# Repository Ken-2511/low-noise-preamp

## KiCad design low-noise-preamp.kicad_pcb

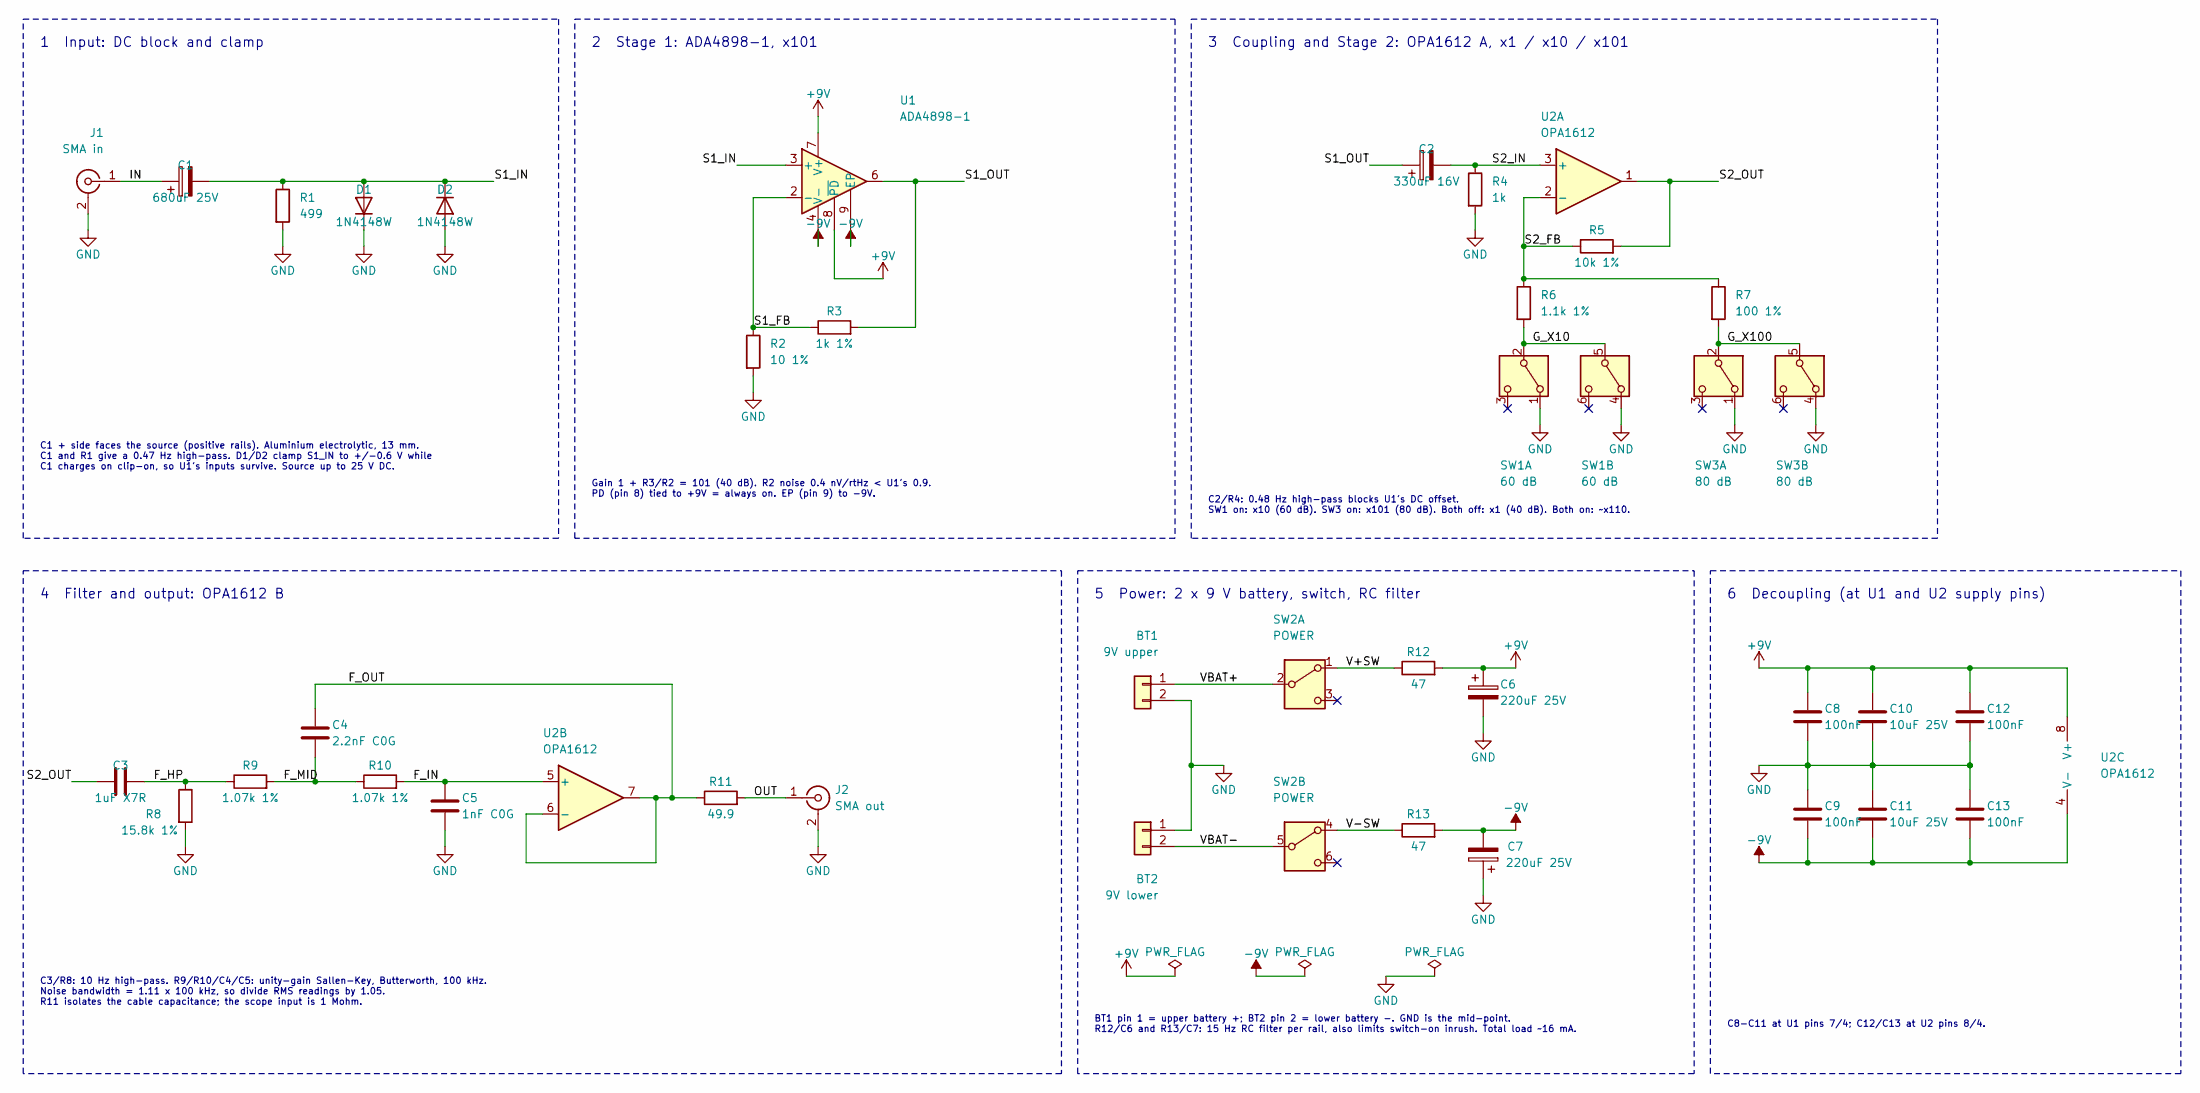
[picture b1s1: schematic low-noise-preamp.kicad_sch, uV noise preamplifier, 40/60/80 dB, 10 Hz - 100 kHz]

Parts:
BT1: 9V upper; JST_XH_B2B-XH-A_1x02_P2.50mm_Vertical
BT2: 9V lower; JST_XH_B2B-XH-A_1x02_P2.50mm_Vertical
C1: 680uF 25V; CP_Radial_D13.0mm_P5.00mm
C2: 330uF 16V; CP_Radial_D8.0mm_P3.50mm
C3: 1uF X7R; C_0805_2012Metric_Pad1.18x1.45mm_HandSolder
C4: 2.2nF C0G; C_0603_1608Metric_Pad1.08x0.95mm_HandSolder
C5: 1nF C0G; C_0603_1608Metric_Pad1.08x0.95mm_HandSolder
C6, C7: 220uF 25V; CP_Radial_D8.0mm_P3.50mm
C8, C9, C12, C13: 100nF; C_0603_1608Metric_Pad1.08x0.95mm_HandSolder
C10, C11: 10uF 25V; C_0805_2012Metric_Pad1.18x1.45mm_HandSolder
D1, D2: 1N4148W; D_SOD-123
J1: SMA in; SMA_Samtec_SMA-J-P-H-ST-EM1_EdgeMount
J2: SMA out; SMA_Samtec_SMA-J-P-H-ST-EM1_EdgeMount
R1: 499; R_0603_1608Metric_Pad0.98x0.95mm_HandSolder
R2: 10 1%; R_0603_1608Metric_Pad0.98x0.95mm_HandSolder
R3: 1k 1%; R_0603_1608Metric_Pad0.98x0.95mm_HandSolder
R4: 1k; R_0603_1608Metric_Pad0.98x0.95mm_HandSolder
R5: 10k 1%; R_0603_1608Metric_Pad0.98x0.95mm_HandSolder
R6: 1.1k 1%; R_0603_1608Metric_Pad0.98x0.95mm_HandSolder
R7: 100 1%; R_0603_1608Metric_Pad0.98x0.95mm_HandSolder
R8: 15.8k 1%; R_0603_1608Metric_Pad0.98x0.95mm_HandSolder
R9, R10: 1.07k 1%; R_0603_1608Metric_Pad0.98x0.95mm_HandSolder
R11: 49.9; R_0603_1608Metric_Pad0.98x0.95mm_HandSolder
R12, R13: 47; R_0805_2012Metric_Pad1.20x1.40mm_HandSolder
SW1: 60 dB; SW_Slide_DPDT_MSS-22D18
SW2: POWER; SW_Slide_DPDT_MSS-22D18
SW3: 80 dB; SW_Slide_DPDT_MSS-22D18
U1: ADA4898-1; SOIC-8-1EP_3.9x4.9mm_P1.27mm_EP2.29x3mm
U2: OPA1612; SOIC-8_3.9x4.9mm_P1.27mm

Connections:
+9V: C6.1, C8.1, C10.1, C12.1, R12.2, U1.7 (V+), U1.8 (~PD), U2.8 (V+)
-9V: C7.2, C9.2, C11.2, C13.2, R13.2, U1.4 (V-), U1.9 (EP), U2.4 (V-)
/F_HP: C3.2, R8.1, R9.1
/F_IN: C5.1, R10.2, U2.5 (+)
/F_MID: C4.2, R9.2, R10.1
/F_OUT: C4.1, R11.1, U2.6 (-), U2.7
/G_X10: R6.2, SW1.2 (B), SW1.5 (B)
/G_X100: R7.2, SW3.2 (B), SW3.5 (B)
/IN: C1.1, J1.1 (In)
/OUT: J2.1 (In), R11.2
/S1_FB: R2.1, R3.1, U1.2 (-)
/S1_IN: C1.2, D1.2 (A), D2.1 (K), R1.1, U1.3 (+)
/S1_OUT: C2.1, R3.2, U1.6
/S2_FB: R5.1, R6.1, R7.1, U2.2 (-)
/S2_IN: C2.2, R4.1, U2.3 (+)
/S2_OUT: C3.1, R5.2, U2.1
/V+SW: R12.1, SW2.1 (A)
/V-SW: R13.1, SW2.4 (A)
/VBAT+: BT1.1, SW2.2 (B)
/VBAT-: BT2.2, SW2.5 (B)
GND: BT1.2, BT2.1, C5.2, C6.2, C7.1, C8.2, C9.1, C10.2, C11.1, C12.2, C13.1, D1.1 (K), D2.2 (A), J1.2 (Ext), J2.2 (Ext), R1.2, R2.2, R4.2, R8.2, SW1.1 (A), SW1.4 (A), SW3.1 (A), SW3.4 (A); also elsewhere on the board

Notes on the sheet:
1 Input: DC block and clamp
C1 + side faces the source (positive rails). Aluminium electrolytic, 13 mm. C1 and R1 give a 0.47 Hz high-pass. D1/D2 clamp S1_IN to +/-0.6 V while C1 charges on clip-on, so U1's inputs survive. Source up to 25 V DC.
2 Stage 1: ADA4898-1, x101
Gain 1 + R3/R2 = 101 (40 dB). R2 noise 0.4 nV/rtHz < U1's 0.9. PD (pin 8) tied to +9V = always on. EP (pin 9) to -9V.
3 Coupling and Stage 2: OPA1612 A, x1 / x10 / x101
C2/R4: 0.48 Hz high-pass blocks U1's DC offset. SW1 on: x10 (60 dB). SW3 on: x101 (80 dB). Both off: x1 (40 dB). Both on: ~x110.
4 Filter and output: OPA1612 B
C3/R8: 10 Hz high-pass. R9/R10/C4/C5: unity-gain Sallen-Key, Butterworth, 100 kHz. Noise bandwidth = 1.11 x 100 kHz, so divide RMS readings by 1.05. R11 isolates the cable capacitance; the scope input is 1 Mohm.
5 Power: 2 x 9 V battery, switch, RC filter
BT1 pin 1 = upper battery +; BT2 pin 2 = lower battery -. GND is the mid-point. R12/C6 and R13/C7: 15 Hz RC filter per rail, also limits switch-on inrush. Total load ~16 mA.
6 Decoupling (at U1 and U2 supply pins)
C8-C11 at U1 pins 7/4; C12/C13 at U2 pins 8/4.

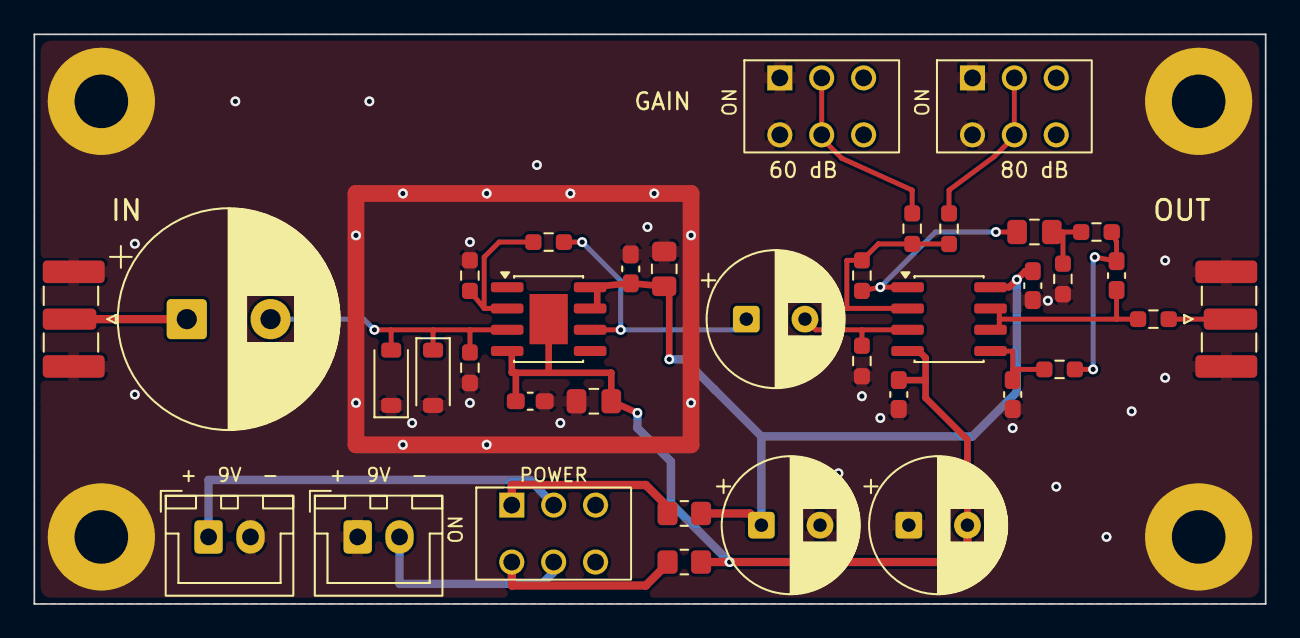
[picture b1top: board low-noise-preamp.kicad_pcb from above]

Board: 2 copper layers, 73.5 x 34.0 mm, 41 parts (0 on the bottom side), 21 nets.

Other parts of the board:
H1, H2, H3, H4: M3; MountingHole_3.2mm_M3_Pad

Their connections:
GND: H1.1, H2.1, H3.1, H4.1; also elsewhere on the board

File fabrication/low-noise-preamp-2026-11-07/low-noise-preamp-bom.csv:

"Refs","Value","Footprint","Qty"
"BT1","9V upper","Connector_JST:JST_XH_B2B-XH-A_1x02_P2.50mm_Vertical","1"
"BT2","9V lower","Connector_JST:JST_XH_B2B-XH-A_1x02_P2.50mm_Vertical","1"
"C1","680uF 25V","Capacitor_THT:CP_Radial_D13.0mm_P5.00mm","1"
"C2","330uF 16V","Capacitor_THT:CP_Radial_D8.0mm_P3.50mm","1"
"C3","1uF X7R","Capacitor_SMD:C_0805_2012Metric_Pad1.18x1.45mm_HandSolder","1"
"C4","2.2nF C0G","Capacitor_SMD:C_0603_1608Metric_Pad1.08x0.95mm_HandSolder","1"
"C5","1nF C0G","Capacitor_SMD:C_0603_1608Metric_Pad1.08x0.95mm_HandSolder","1"
"C6,C7","220uF 25V","Capacitor_THT:CP_Radial_D8.0mm_P3.50mm","2"
"C8,C9,C12,C13","100nF","Capacitor_SMD:C_0603_1608Metric_Pad1.08x0.95mm_HandSolder","4"
"C10,C11","10uF 25V","Capacitor_SMD:C_0805_2012Metric_Pad1.18x1.45mm_HandSolder","2"
"D1,D2","1N4148W","Diode_SMD:D_SOD-123","2"
"J1","SMA in","Connector_Coaxial:SMA_Samtec_SMA-J-P-H-ST-EM1_EdgeMount","1"
"J2","SMA out","Connector_Coaxial:SMA_Samtec_SMA-J-P-H-ST-EM1_EdgeMount","1"
"R1","499","Resistor_SMD:R_0603_1608Metric_Pad0.98x0.95mm_HandSolder","1"
"R2","10 1%","Resistor_SMD:R_0603_1608Metric_Pad0.98x0.95mm_HandSolder","1"
"R3","1k 1%","Resistor_SMD:R_0603_1608Metric_Pad0.98x0.95mm_HandSolder","1"
"R4","1k","Resistor_SMD:R_0603_1608Metric_Pad0.98x0.95mm_HandSolder","1"
"R5","10k 1%","Resistor_SMD:R_0603_1608Metric_Pad0.98x0.95mm_HandSolder","1"
"R6","1.1k 1%","Resistor_SMD:R_0603_1608Metric_Pad0.98x0.95mm_HandSolder","1"
"R7","100 1%","Resistor_SMD:R_0603_1608Metric_Pad0.98x0.95mm_HandSolder","1"
"R8","15.8k 1%","Resistor_SMD:R_0603_1608Metric_Pad0.98x0.95mm_HandSolder","1"
"R9,R10","1.07k 1%","Resistor_SMD:R_0603_1608Metric_Pad0.98x0.95mm_HandSolder","2"
"R11","49.9","Resistor_SMD:R_0603_1608Metric_Pad0.98x0.95mm_HandSolder","1"
"R12,R13","47","Resistor_SMD:R_0805_2012Metric_Pad1.20x1.40mm_HandSolder","2"
"SW1","60 dB","low-noise-preamp:SW_Slide_DPDT_MSS-22D18","1"
"SW2","POWER","low-noise-preamp:SW_Slide_DPDT_MSS-22D18","1"
"SW3","80 dB","low-noise-preamp:SW_Slide_DPDT_MSS-22D18","1"
"U1","ADA4898-1","Package_SO:SOIC-8-1EP_3.9x4.9mm_P1.27mm_EP2.29x3mm","1"
"U2","OPA1612","Package_SO:SOIC-8_3.9x4.9mm_P1.27mm","1"
